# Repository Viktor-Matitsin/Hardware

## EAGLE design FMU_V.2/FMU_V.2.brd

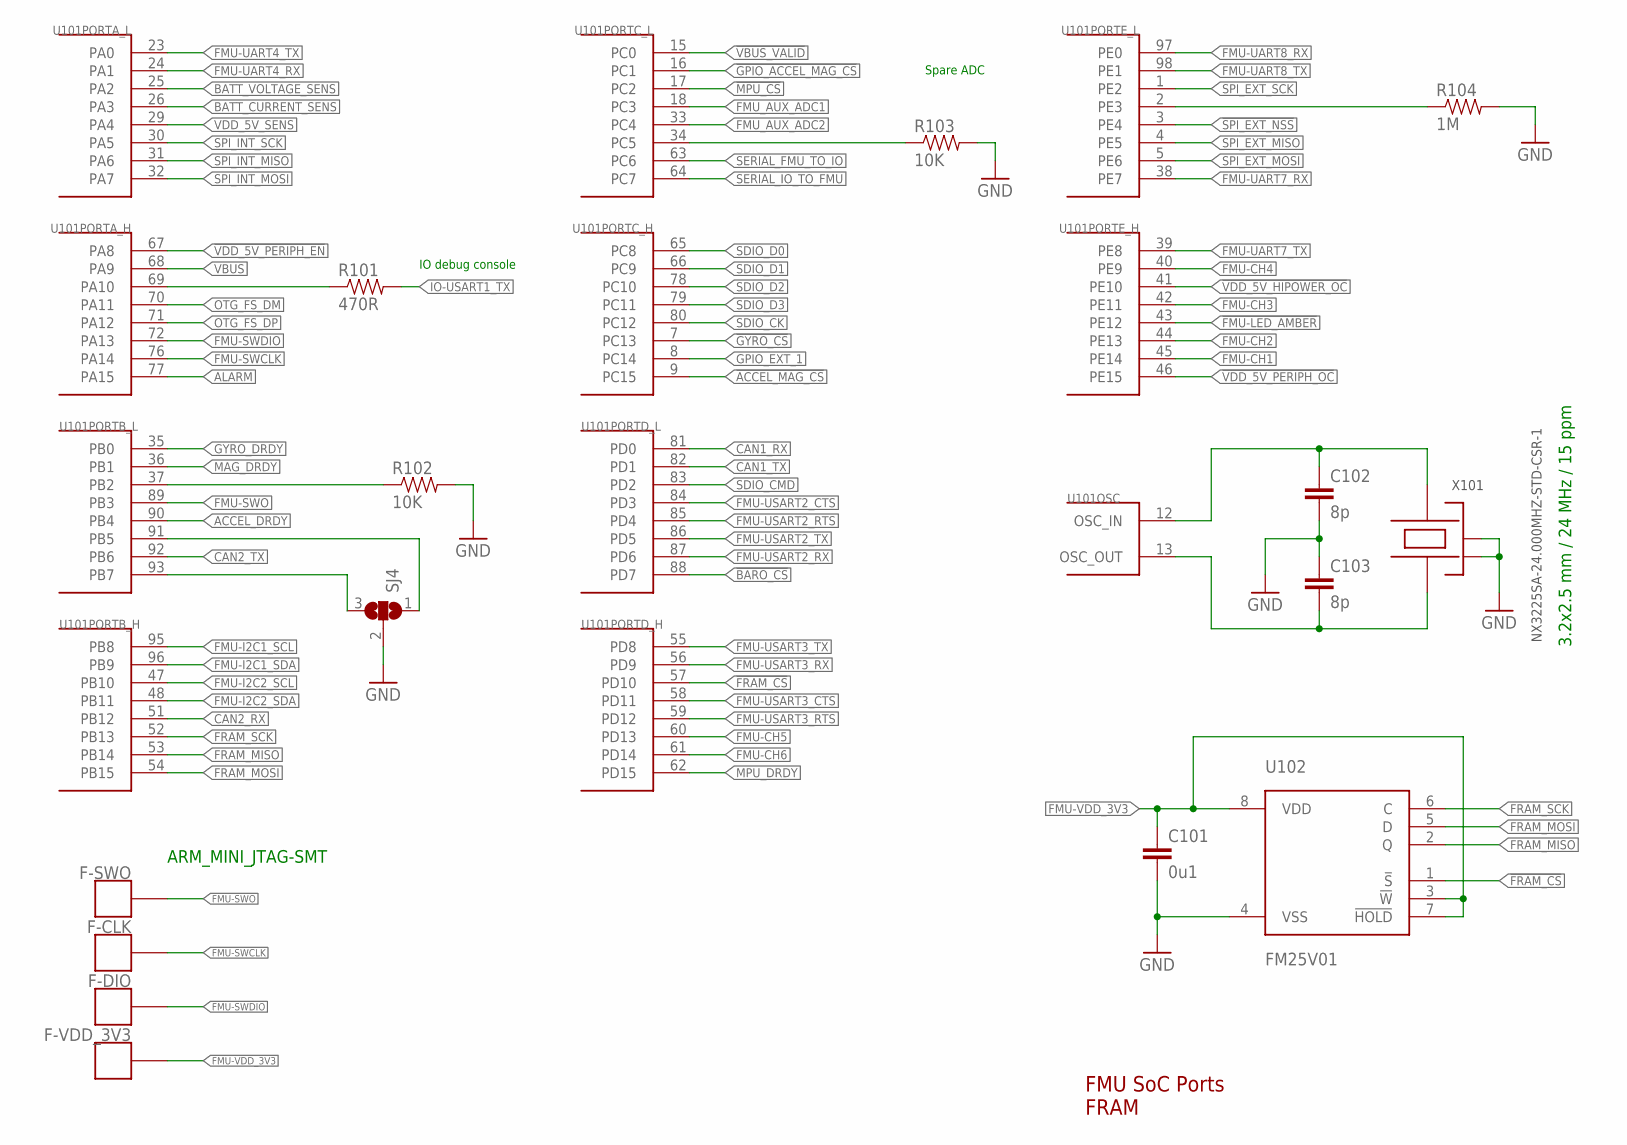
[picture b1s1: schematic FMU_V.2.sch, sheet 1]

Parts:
C101: 0u1; 0603-CAP
C102, C103: 8p; 0603-CAP
F-CLK: PAD.04; PAD.04X.04
F-DIO: PAD.04; PAD.04X.04
F-SWO: PAD.04; PAD.04X.04
F-VDD_3V3: PAD.04; PAD.04X.04
R101: 470R; 0603-RES
R102, R103: 10K; 0603-RES
R104: 1M; 0603-RES
SJ4: SJ2W; SJ_2
U101: STM32F4X7VX; TQFP100; PARTNO STM32F427VI
U102: FM25V01; SO08; PARTNO FM25V01-G
X101: NX3225SA-24.000MHZ-STD-CSR-1; OSCILLATOR-3.2X2.5; PARTNO NX3225SA-24.000000MHZ

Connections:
!ACCEL_MAG_CS: U101.9 (PC15); also elsewhere on the board
!BARO_CS: U101.88 (PD7); also elsewhere on the board
!FMU-LED_AMBER: U101.43 (PE12); also elsewhere on the board
!FRAM_CS: U101.57 (PD10), U102.1 (!S)
!GPIO_ACCEL_MAG_CS: U101.16 (PC1); also elsewhere on the board
!GYRO_CS: U101.7 (PC13); also elsewhere on the board
!MPU_CS: U101.17 (PC2); also elsewhere on the board
!SPI_EXT_NSS: U101.3 (PE4); also elsewhere on the board
!VBUS_VALID: U101.15 (PC0)
!VDD_5V_HIPOWER_OC: U101.41 (PE10); also elsewhere on the board
!VDD_5V_PERIPH_EN: U101.67 (PA8); also elsewhere on the board
!VDD_5V_PERIPH_OC: U101.46 (PE15); also elsewhere on the board
!VDD_BRICK_VALID: SJ4.1, U101.91 (PB5)
!VDD_SERVO_VALID: SJ4.3, U101.93 (PB7)
ACCEL_DRDY: U101.90 (PB4); also elsewhere on the board
ALARM: U101.77 (PA15); also elsewhere on the board
BATT_CURRENT_SENS: U101.26 (PA3); also elsewhere on the board
BATT_VOLTAGE_SENS: U101.25 (PA2); also elsewhere on the board
CAN1_RX: U101.81 (PD0); also elsewhere on the board
CAN1_TX: U101.82 (PD1); also elsewhere on the board
CAN2_RX: U101.51 (PB12); also elsewhere on the board
CAN2_TX: U101.92 (PB6); also elsewhere on the board
FMU-CH1: U101.45 (PE14); also elsewhere on the board
FMU-CH2: U101.44 (PE13); also elsewhere on the board
FMU-CH3: U101.42 (PE11); also elsewhere on the board
FMU-CH4: U101.40 (PE9); also elsewhere on the board
FMU-CH5: U101.60 (PD13); also elsewhere on the board
FMU-CH6: U101.61 (PD14); also elsewhere on the board
FMU-I2C1_SCL: U101.95 (PB8); also elsewhere on the board
FMU-I2C1_SDA: U101.96 (PB9); also elsewhere on the board
FMU-I2C2_SCL: U101.47 (PB10); also elsewhere on the board
FMU-I2C2_SDA: U101.48 (PB11); also elsewhere on the board
FMU-SWCLK: F-CLK.P$1, U101.76 (PA14)
FMU-SWDIO: F-DIO.P$1, U101.72 (PA13)
FMU-SWO: F-SWO.P$1, U101.89 (PB3)
FMU-UART4_RX: U101.24 (PA1); also elsewhere on the board
FMU-UART4_TX: U101.23 (PA0); also elsewhere on the board
FMU-UART7_RX: U101.38 (PE7); also elsewhere on the board
FMU-UART7_TX: U101.39 (PE8); also elsewhere on the board
FMU-UART8_RX: U101.97 (PE0); also elsewhere on the board
FMU-UART8_TX: U101.98 (PE1); also elsewhere on the board
FMU-USART2_CTS: U101.84 (PD3); also elsewhere on the board
FMU-USART2_RTS: U101.85 (PD4); also elsewhere on the board
FMU-USART2_RX: U101.87 (PD6); also elsewhere on the board
FMU-USART2_TX: U101.86 (PD5); also elsewhere on the board
FMU-USART3_CTS: U101.58 (PD11)
FMU-USART3_RTS: U101.59 (PD12)
FMU-USART3_RX: U101.56 (PD9); also elsewhere on the board
FMU-USART3_TX: U101.55 (PD8); also elsewhere on the board
FMU-VDD_3V3: C101.P$1 (1), F-VDD_3V3.P$1, U102.3 (!W), U102.7 (!HOLD), U102.8 (VDD); also elsewhere on the board
FMU_AUX_ADC1: U101.18 (PC3); also elsewhere on the board
FMU_AUX_ADC2: U101.33 (PC4); also elsewhere on the board
FRAM_MISO: U101.53 (PB14), U102.2 (Q)
FRAM_MOSI: U101.54 (PB15), U102.5 (D)
FRAM_SCK: U101.52 (PB13), U102.6 (C)
GND: C101.P$2 (2), C102.P$2 (2), C103.P$1 (1), R102.2, R103.2, R104.2, SJ4.2, U102.4 (VSS), X101.2 (NC_2), X101.4 (NC_4); also elsewhere on the board
GPIO_EXT_1: U101.8 (PC14); also elsewhere on the board
GYRO_DRDY: U101.35 (PB0); also elsewhere on the board
IO-USART1_TX: R101.2; also elsewhere on the board
MAG_DRDY: U101.36 (PB1); also elsewhere on the board
MPU_DRDY: U101.62 (PD15); also elsewhere on the board
unnamed: C103.P$2 (2), U101.13 (OSC_OUT), X101.1
unnamed: C102.P$1 (1), U101.12 (OSC_IN), X101.3
unnamed: R104.1, U101.2 (PE3)
unnamed: R103.1, U101.34 (PC5)
unnamed: R101.1, U101.69 (PA10)
OTG_FS_DM: U101.70 (PA11); also elsewhere on the board
OTG_FS_DP: U101.71 (PA12); also elsewhere on the board
PC5: R102.1, U101.37 (PB2)
SDIO_CK: U101.80 (PC12); also elsewhere on the board
SDIO_CMD: U101.83 (PD2); also elsewhere on the board
SDIO_D0: U101.65 (PC8); also elsewhere on the board
SDIO_D1: U101.66 (PC9); also elsewhere on the board
SDIO_D2: U101.78 (PC10); also elsewhere on the board
SDIO_D3: U101.79 (PC11); also elsewhere on the board
SERIAL_FMU_TO_IO: U101.63 (PC6); also elsewhere on the board
SERIAL_IO_TO_FMU: U101.64 (PC7); also elsewhere on the board
SPI_EXT_MISO: U101.4 (PE5); also elsewhere on the board
SPI_EXT_MOSI: U101.5 (PE6); also elsewhere on the board
SPI_EXT_SCK: U101.1 (PE2); also elsewhere on the board
SPI_INT_MISO: U101.31 (PA6); also elsewhere on the board
SPI_INT_MOSI: U101.32 (PA7); also elsewhere on the board
SPI_INT_SCK: U101.30 (PA5); also elsewhere on the board
VBUS: U101.68 (PA9); also elsewhere on the board
VDD_5V_SENS: U101.29 (PA4); also elsewhere on the board

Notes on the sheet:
FMU SoC Ports FRAM
IO debug console
Spare ADC
3.2x2.5 mm / 24 MHz / 15 ppm
ARM_MINI_JTAG-SMT

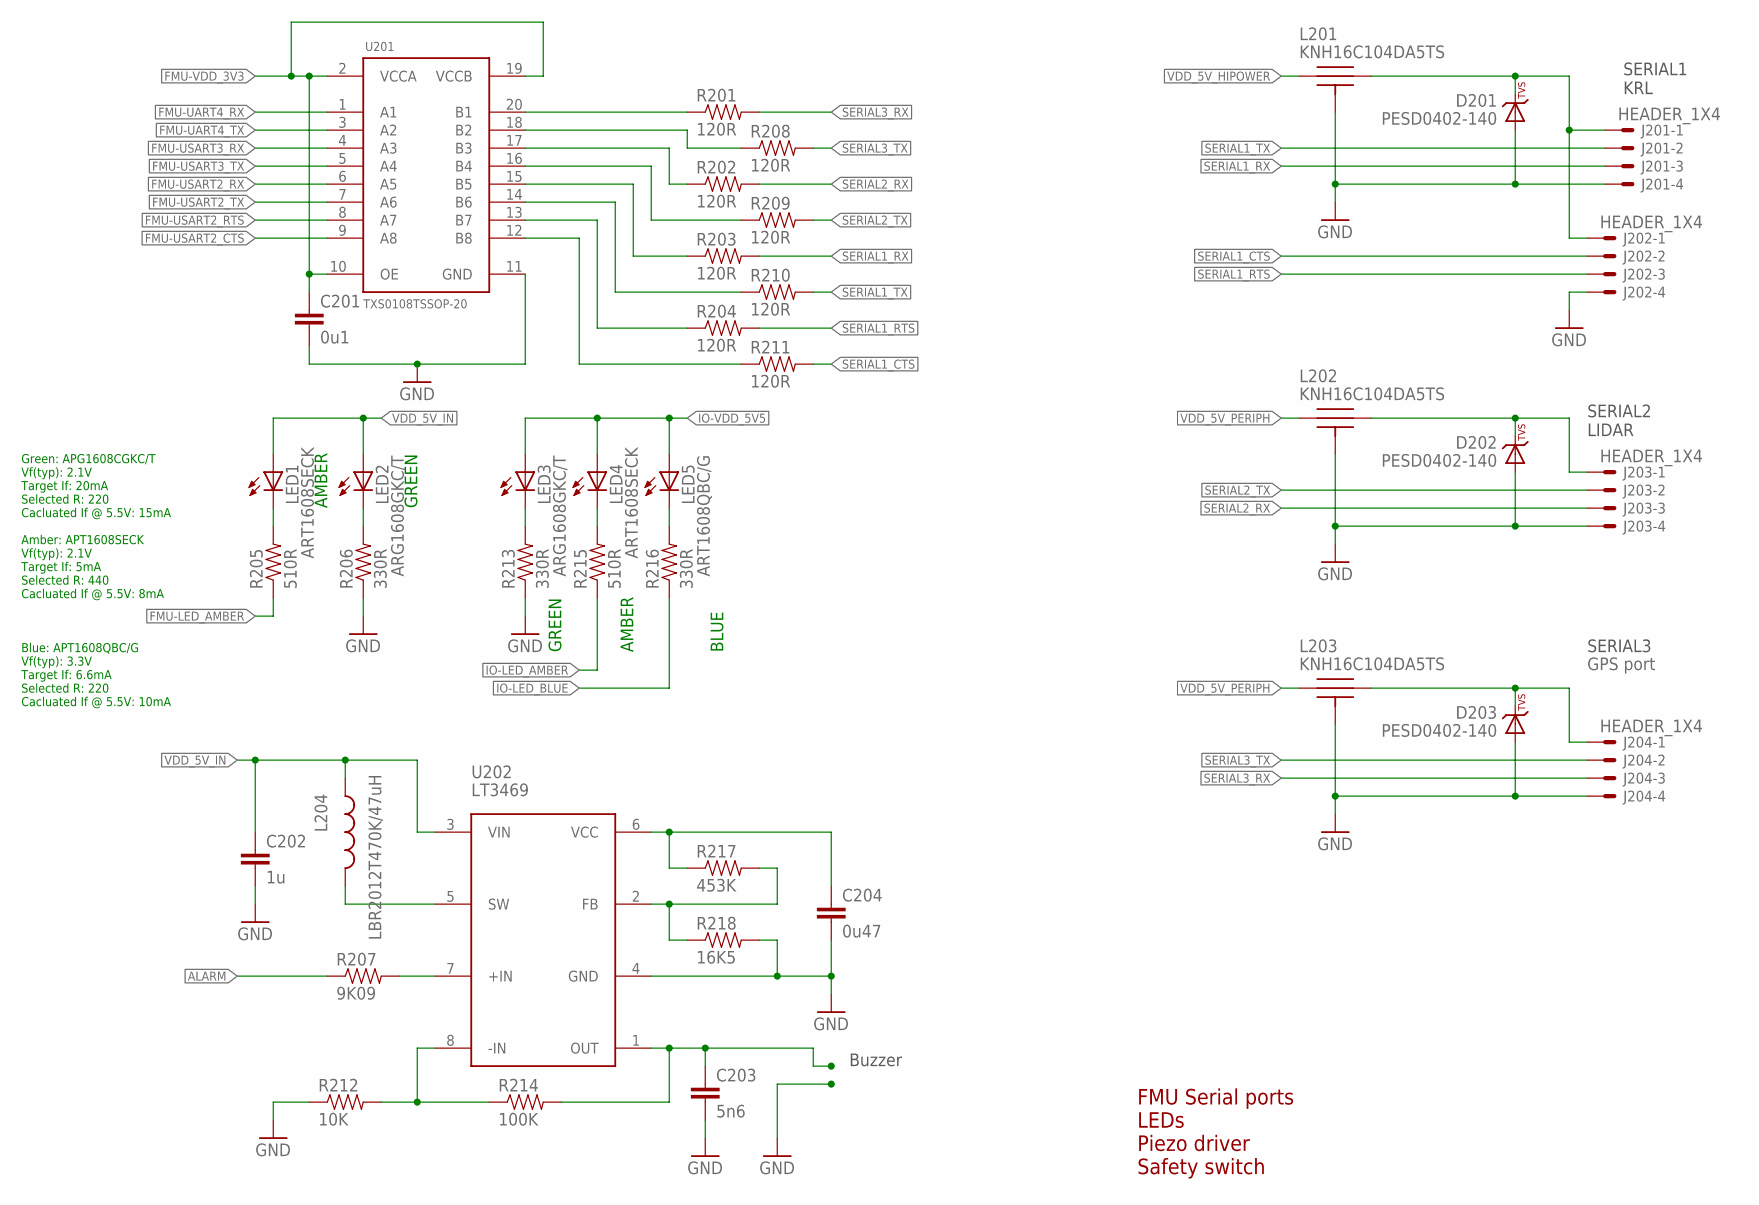
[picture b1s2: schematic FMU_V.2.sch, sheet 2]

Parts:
C201: 0u1; 0603-CAP
C202: 1u; 0603-CAP
C203: 5n6; 0603-CAP
C204: 0u47; 0603-CAP
D201, D202, D203: PESD0402-140; 0402-TVS; PARTNO PESD0402-140
J201, J202, J203, J204: HEADER_1X4; HEADER_2.54MM-1X04
L201, L202, L203: KNH16C104DA5TS; KYOCERA-KNH16-DA; PARTNO KNH16C104DA5TS
L204: LBR2012T470K/47uH; 0805-IND
LED1, LED4: ART1608SECK; 0603-LED
LED2, LED3: ARG1608GKC/T; 0603-LED
LED5: ART1608QBC/G; 0603-LED
R201, R202, R203, R204, R208, R209, R210, R211: 120R; 0603-RES
R205, R215: 510R; 0603-RES
R206, R213, R216: 330R; 0603-RES
R207: 9K09; 0603-RES
R212: 10K; 0603-RES
R214: 100K; 0603-RES
R217: 453K; 0603-RES
R218: 16K5; 0603-RES
U201: TXS0108TSSOP-20; R-PDSO-G20
U202: LT3469; SOT23-8

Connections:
!FMU-LED_AMBER: R205.1; also elsewhere on the board
!IO-LED_AMBER: R215.1; also elsewhere on the board
!IO-LED_BLUE: R216.1; also elsewhere on the board
ALARM: R207.1; also elsewhere on the board
FMU-UART4_RX: U201.1 (A1); also elsewhere on the board
FMU-UART4_TX: U201.3 (A2); also elsewhere on the board
FMU-USART2_CTS: U201.9 (A8); also elsewhere on the board
FMU-USART2_RTS: U201.8 (A7); also elsewhere on the board
FMU-USART2_RX: U201.6 (A5); also elsewhere on the board
FMU-USART2_TX: U201.7 (A6); also elsewhere on the board
FMU-USART3_RX: U201.4 (A3); also elsewhere on the board
FMU-USART3_TX: U201.5 (A4); also elsewhere on the board
FMU-VDD_3V3: C201.P$1 (1), U201.2 (VCCA), U201.10 (OE), U201.19 (VCCB); also elsewhere on the board
GND: C201.P$2 (2), C202.P$2 (2), C203.P$2 (2), C204.P$2 (2), D201.A, D202.A, D203.A, J201.4, J202.4, J203.4, J204.4, L201.P$3, L201.P$4, L201.P$5, L202.P$3, L202.P$4, L202.P$5, L203.P$3, L203.P$4, L203.P$5, R206.1, R212.1, R213.1, R218.2, U201.11 (GND), U202.4 (GND); also elsewhere on the board
IO-VDD_5V5: LED3.A, LED4.A, LED5.A; also elsewhere on the board
unnamed: D201.C, J201.1, J202.1, L201.P$2
unnamed: R201.1, U201.20 (B1)
unnamed: R208.1, U201.18 (B2)
unnamed: R202.1, U201.17 (B3)
unnamed: R209.1, U201.16 (B4)
unnamed: R203.1, U201.15 (B5)
unnamed: R210.1, U201.14 (B6)
unnamed: R204.1, U201.13 (B7)
unnamed: R211.1, U201.12 (B8)
unnamed: LED1.C, R205.2
unnamed: LED2.C, R206.2
unnamed: L204.P$2 (2), U202.5 (SW)
unnamed: LED3.C, R213.2
unnamed: LED4.C, R215.2
unnamed: LED5.C, R216.2
unnamed: D203.C, J204.1, L203.P$2
unnamed: D202.C, J203.1, L202.P$2
unnamed: C203.P$1 (1), R214.2, U202.1 (OUT)
unnamed: R207.2, U202.7 (+IN)
unnamed: R212.2, R214.1, U202.8 (-IN)
unnamed: C204.P$1 (1), R217.1, U202.6 (VCC)
unnamed: R217.2, R218.1, U202.2 (FB)
SERIAL1_CTS: J202.2, R211.2
SERIAL1_RTS: J202.3, R204.2
SERIAL1_RX: J201.3, R203.2
SERIAL1_TX: J201.2, R210.2
SERIAL2_RX: J203.3, R202.2
SERIAL2_TX: J203.2, R209.2
SERIAL3_RX: J204.3, R201.2
SERIAL3_TX: J204.2, R208.2
VDD_5V_HIPOWER: L201.P$1; also elsewhere on the board
VDD_5V_IN: C202.P$1 (1), L204.P$1 (1), LED1.A, LED2.A, U202.3 (VIN); also elsewhere on the board
VDD_5V_PERIPH: L202.P$1, L203.P$1; also elsewhere on the board

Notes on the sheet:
FMU Serial ports LEDs Piezo driver Safety switch
SERIAL2 LIDAR
SERIAL1 KRL
SERIAL3
GPS port
Green: APG1608CGKC/T Vf(typ): 2.1V Target If: 20mA Selected R: 220 Cacluated If @ 5.5V: 15mA Amber: APT1608SECK Vf(typ): 2.1V Target If: 5mA Selected R: 440 Cacluated If @ 5.5V: 8mA Blue: APT1608QBC/G Vf(typ): 3.3V Target If: 6.6mA Selected R: 220 Cacluated If @ 5.5V: 10mA
Buzzer
AMBER
GREEN
BLUE

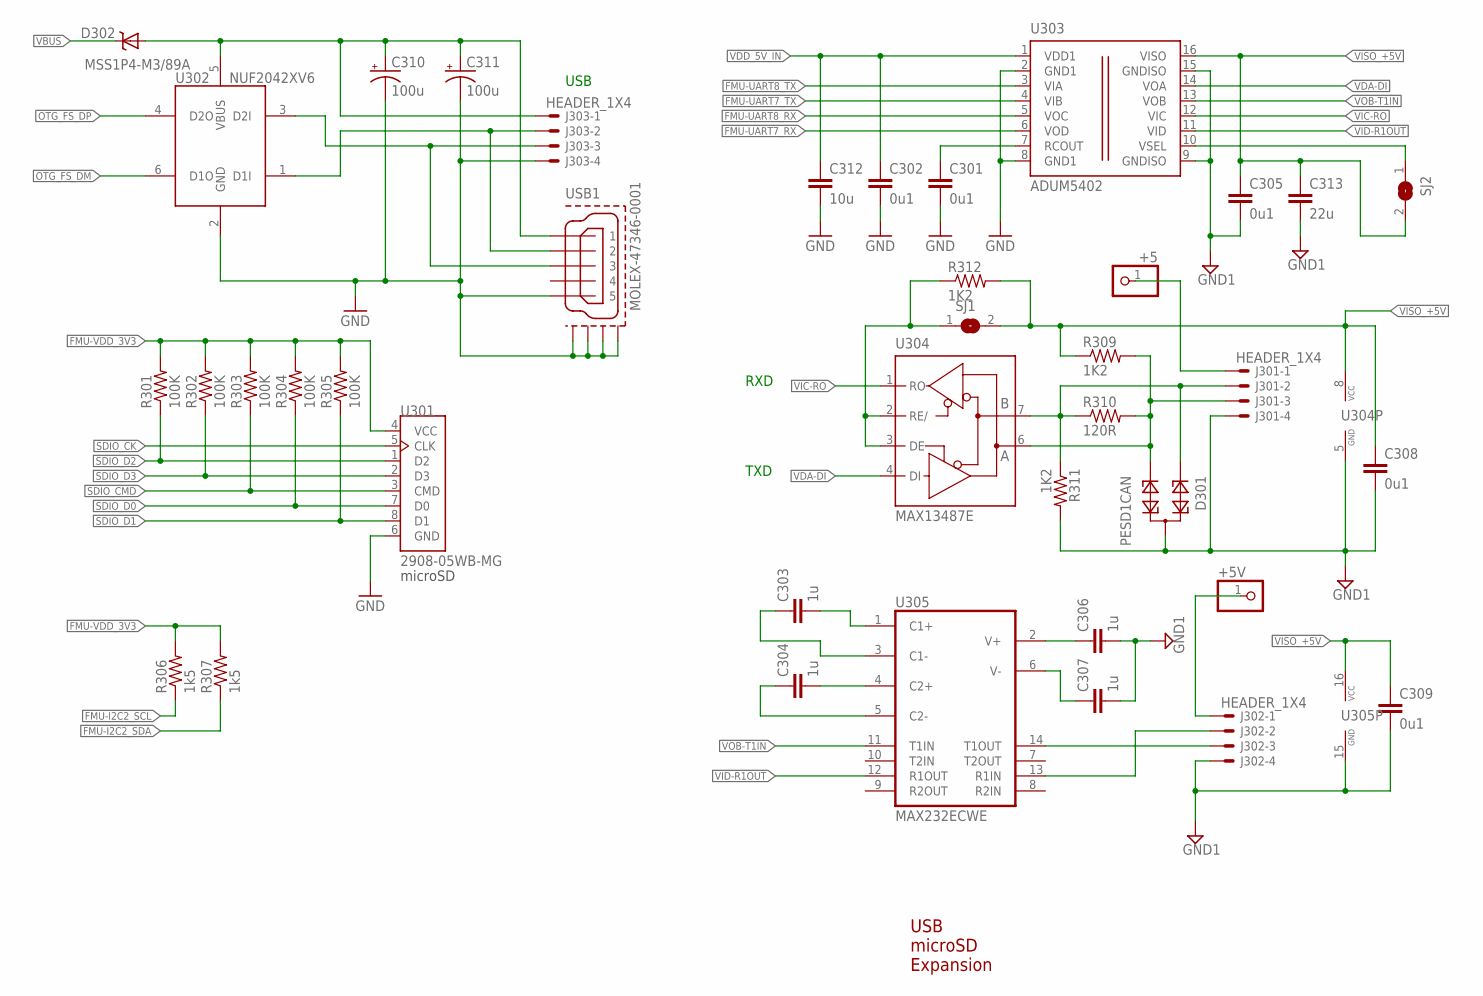
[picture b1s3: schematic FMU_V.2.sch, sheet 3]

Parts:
+5, +5V: PINHD-1X1; 1X01
C301, C302, C305, C308, C309: 0u1; 0603-CAP
C303, C304, C306, C307: 1u; 0805-CAP
C310, C311: 100u; EIA3216
C312: 10u; 0805-CAP
C313: 22u; 0805-CAP
D301: PESD1CAN; SOT23
D302: MSS1P4-M3/89A; MICROSMP
J301, J302, J303: HEADER_1X4; HEADER_2.54MM-1X04
R301, R302, R303, R304, R305: 100K; 0603-RES
R306, R307: 1k5; 0603-RES
R309, R311, R312: 1K2; 0603-RES
R310: 120R; 0805
SJ1, SJ2: SJ
U301: 2908-05WB-MG; MICROSD; PARTNO 2908-05WB-MG
U302: NUF2042XV6; SOT563-6; PARTNO NUF2042XV6T1G
U303: ADUM5402; SO-16W
U304: MAX13487E; SO08
U305: MAX232ECWE; SO16L
USB1: MOLEX-47346-0001

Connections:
1: C310.A (+), C311.A (+), D302.ANODE (A), J303.1, U302.5 (VBUS), USB1.VBUS (1)
FMU-I2C2_SCL: R306.1; also elsewhere on the board
FMU-I2C2_SDA: R307.1; also elsewhere on the board
FMU-UART7_RX: U303.6 (VOD); also elsewhere on the board
FMU-UART7_TX: U303.4 (VIB); also elsewhere on the board
FMU-UART8_RX: U303.5 (VOC); also elsewhere on the board
FMU-UART8_TX: U303.3 (VIA); also elsewhere on the board
FMU-VDD_3V3: R301.2, R302.2, R303.2, R304.2, R305.2, R306.2, R307.2, U301.4 (VCC); also elsewhere on the board
GND: C301.P$2 (2), C302.P$2 (2), C310.C (-), C311.C (-), C312.P$2 (2), J303.4, U301.6 (GND), U302.2 (GND), U303.2 (GND1), U303.8 (GND1), USB1.GND (5), USB1.GND1, USB1.GND2, USB1.GND3, USB1.GND4; also elsewhere on the board
GND1: C305.P$2 (2), C306.P$2 (2), C307.P$2 (2), C308.P$2 (2), C309.P$2 (2), C313.P$2 (2), D301.3, J301.4, J302.4, R311.2, U303.9 (GNDISO), U303.15 (GNDISO), U304.5 (GND), U305.15 (GND); also elsewhere on the board
unnamed: SJ2.1, U303.10 (VSEL)
unnamed: C304.P$2 (2), U305.4 (C2+)
unnamed: C304.P$1 (1), U305.5 (C2-)
unnamed: C303.P$1 (1), U305.3 (C1-)
unnamed: R312.1, SJ1.1, U304.2 (RE/), U304.3 (DE)
unnamed: C301.P$1 (1), U303.7 (RCOUT)
unnamed: C303.P$2 (2), U305.1 (C1+)
unnamed: C306.P$1 (1), U305.2 (V+)
unnamed: D301.1, J301.2, R310.1, R311.1, U304.7 (B)
unnamed: D301.2, J301.3, R309.2, R310.2, U304.6 (A)
unnamed: C307.P$1 (1), U305.6 (V-)
unnamed: J302.3, U305.14 (T1OUT)
unnamed: J302.2, U305.13 (R1IN)
unnamed: +5.1, J301.1
unnamed: +5V.1, J302.1
OTG_DM1: J303.2, U302.1 (D1I), USB1.D- (2)
OTG_DP1: J303.3, U302.3 (D2I), USB1.D+ (3)
OTG_FS_DM: U302.6 (D1O); also elsewhere on the board
OTG_FS_DP: U302.4 (D2O); also elsewhere on the board
SDIO_CK: U301.5 (CLK); also elsewhere on the board
SDIO_CMD: R303.1, U301.3 (CMD); also elsewhere on the board
SDIO_D0: R304.1, U301.7 (D0); also elsewhere on the board
SDIO_D1: R305.1, U301.8 (D1); also elsewhere on the board
SDIO_D2: R301.1, U301.1 (D2); also elsewhere on the board
SDIO_D3: R302.1, U301.2 (D3); also elsewhere on the board
VBUS: D302.CATHODE (C); also elsewhere on the board
VDA-DI: U303.14 (VOA), U304.4 (DI)
VDD_5V_IN: C302.P$1 (1), C312.P$1 (1), U303.1 (VDD1); also elsewhere on the board
VIC-RO: U303.12 (VIC), U304.1 (RO)
VID-R1OUT: U303.11 (VID), U305.12 (R1OUT)
VISO_+5V: C305.P$1 (1), C308.P$1 (1), C309.P$1 (1), C313.P$1 (1), R309.1, R312.2, SJ1.2, SJ2.2, U303.16 (VISO), U304.8 (VCC), U305.16 (VCC)
VOB-T1IN: U303.13 (VOB), U305.11 (T1IN)

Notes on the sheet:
USB microSD Expansion
microSD
USB
RXD
TXD

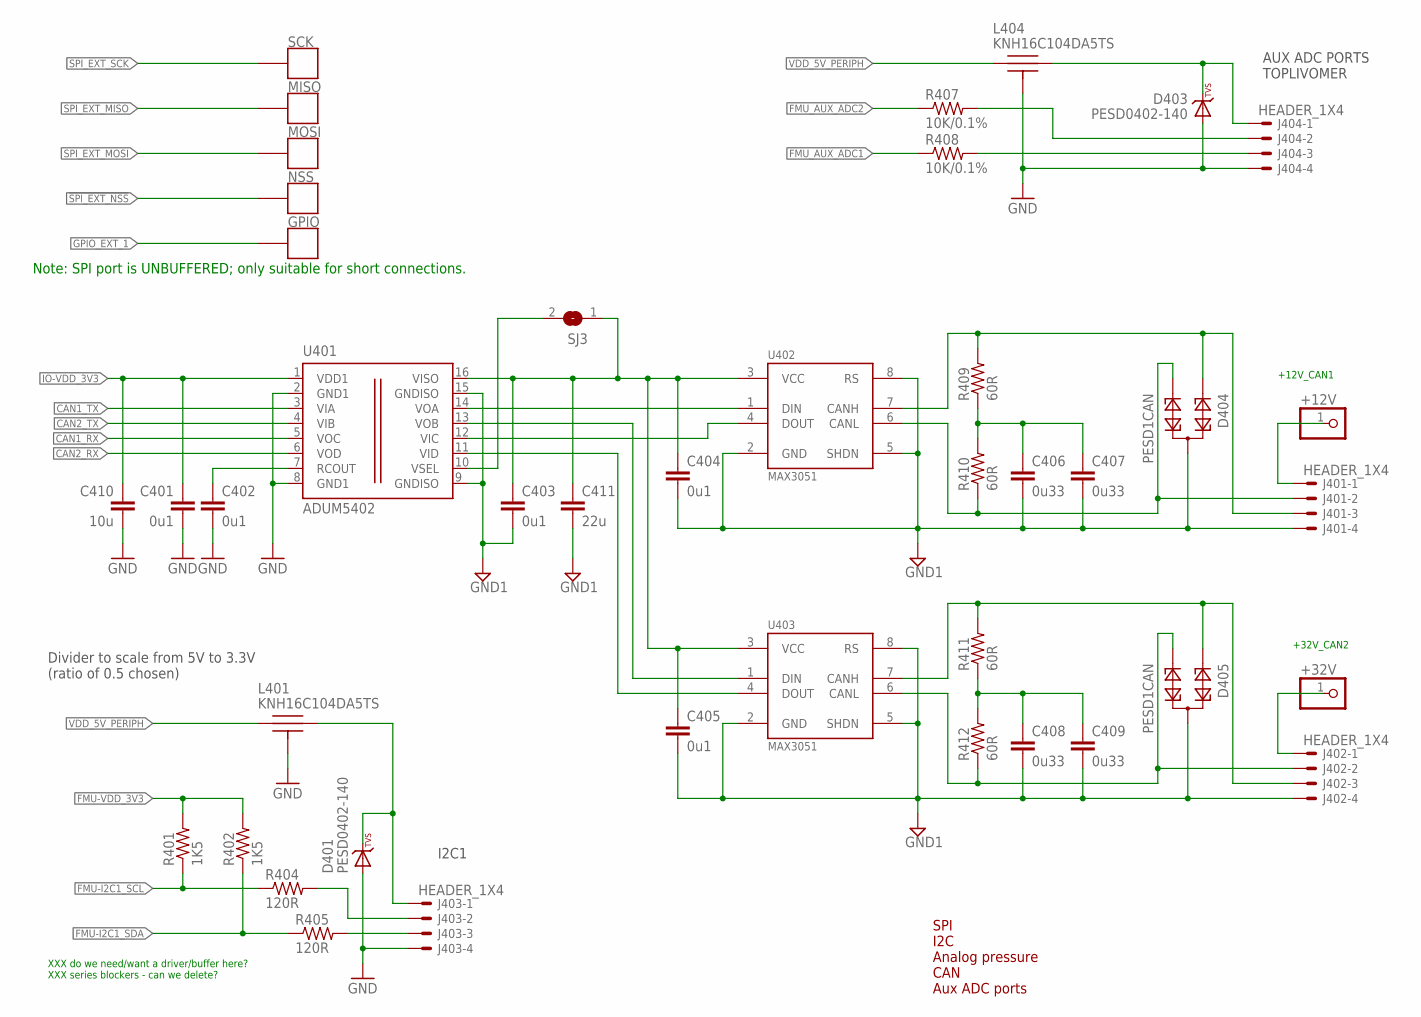
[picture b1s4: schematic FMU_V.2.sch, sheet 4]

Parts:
+12V, +32V: PINHD-1X1; 1X01
C401, C402, C403, C404, C405: 0u1; 0603-CAP
C406, C407, C408, C409: 0u33; 1210
C410: 10u; 0805-CAP
C411: 22u; 0805-CAP
D401, D403: PESD0402-140; 0402-TVS; PARTNO PESD0402-140
D404, D405: PESD1CAN; SOT23
GPIO: PAD.04; PAD.04X.04
J401, J402, J403, J404: HEADER_1X4; HEADER_2.54MM-1X04
L401, L404: KNH16C104DA5TS; KYOCERA-KNH16-DA; PARTNO KNH16C104DA5TS
MISO: PAD.04; PAD.04X.04
MOSI: PAD.04; PAD.04X.04
NSS: PAD.04; PAD.04X.04
R401, R402: 1K5; 0603-RES
R404, R405: 120R; 0603-RES
R407, R408: 10K/0.1%; 0603-RES
R409, R410, R411, R412: 60R; 0805
SCK: PAD.04; PAD.04X.04
SJ3: SJ
U401: ADUM5402; SO-16W
U402, U403: MAX3051; SOT23-8; PARTNO MAX3051EKA

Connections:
!SPI_EXT_NSS: NSS.P$1; also elsewhere on the board
CAN1_RX: U401.5 (VOC); also elsewhere on the board
CAN1_TX: U401.3 (VIA); also elsewhere on the board
CAN2_RX: U401.6 (VOD); also elsewhere on the board
CAN2_TX: U401.4 (VIB); also elsewhere on the board
FMU-I2C1_SCL: R401.1, R404.1; also elsewhere on the board
FMU-I2C1_SDA: R402.1, R405.1; also elsewhere on the board
FMU-VDD_3V3: R401.2, R402.2; also elsewhere on the board
FMU_AUX_ADC1: R408.1; also elsewhere on the board
FMU_AUX_ADC2: R407.1; also elsewhere on the board
FMU_AUX_ADC2_PROT: J404.2, R407.2
GND: C401.P$2 (2), C402.P$2 (2), C410.P$2 (2), D401.A, D403.A, J403.4, J404.4, L401.P$3, L401.P$4, L401.P$5, L404.P$3, L404.P$4, L404.P$5, U401.2 (GND1), U401.8 (GND1); also elsewhere on the board
GND1: C403.P$2 (2), C404.P$2 (2), C405.P$2 (2), C406.2, C407.2, C408.2, C409.2, C411.P$2 (2), D404.3, D405.3, J401.4, J402.4, U401.9 (GNDISO), U401.15 (GNDISO), U402.2 (GND), U402.5 (SHDN), U402.8 (RS), U403.2 (GND), U403.5 (SHDN), U403.8 (RS); also elsewhere on the board
GPIO_EXT_1: GPIO.P$1; also elsewhere on the board
IO-VDD_3V3: C401.P$1 (1), C410.P$1 (1), U401.1 (VDD1); also elsewhere on the board
unnamed: J404.3, R408.2
unnamed: C406.1, C407.1, R409.1, R410.2
unnamed: D405.1, J402.3, R411.2, U403.7 (CANH)
unnamed: D404.1, J401.3, R409.2, U402.7 (CANH)
unnamed: SJ3.2, U401.10 (VSEL)
unnamed: U401.13 (VOB), U403.1 (DIN)
unnamed: D405.2, J402.2, R412.1, U403.6 (CANL)
unnamed: D404.2, J401.2, R410.1, U402.6 (CANL)
unnamed: U401.14 (VOA), U402.1 (DIN)
unnamed: U401.12 (VIC), U402.4 (DOUT)
unnamed: U401.11 (VID), U403.4 (DOUT)
unnamed: C402.P$1 (1), U401.7 (RCOUT)
unnamed: J403.2, R404.2
unnamed: C408.1, C409.1, R411.1, R412.2
unnamed: J403.3, R405.2
unnamed: C403.P$1 (1), C404.P$1 (1), C405.P$1 (1), C411.P$1 (1), SJ3.1, U401.16 (VISO), U402.3 (VCC), U403.3 (VCC)
unnamed: D401.C, J403.1, L401.P$2
unnamed: D403.C, J404.1, L404.P$2
P1: +12V.1, J401.1
P2: +32V.1, J402.1
SPI_EXT_MISO: MISO.P$1; also elsewhere on the board
SPI_EXT_MOSI: MOSI.P$1; also elsewhere on the board
SPI_EXT_SCK: SCK.P$1; also elsewhere on the board
VDD_5V_PERIPH: L401.P$1, L404.P$1; also elsewhere on the board

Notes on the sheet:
XXX do we need/want a driver/buffer here? XXX series blockers - can we delete?
I2C1
AUX ADC PORTS TOPLIVOMER
SPI I2C Analog pressure CAN Aux ADC ports
Note: SPI port is UNBUFFERED; only suitable for short connections.
Divider to scale from 5V to 3.3V (ratio of 0.5 chosen)
+12V_CAN1
+32V_CAN2

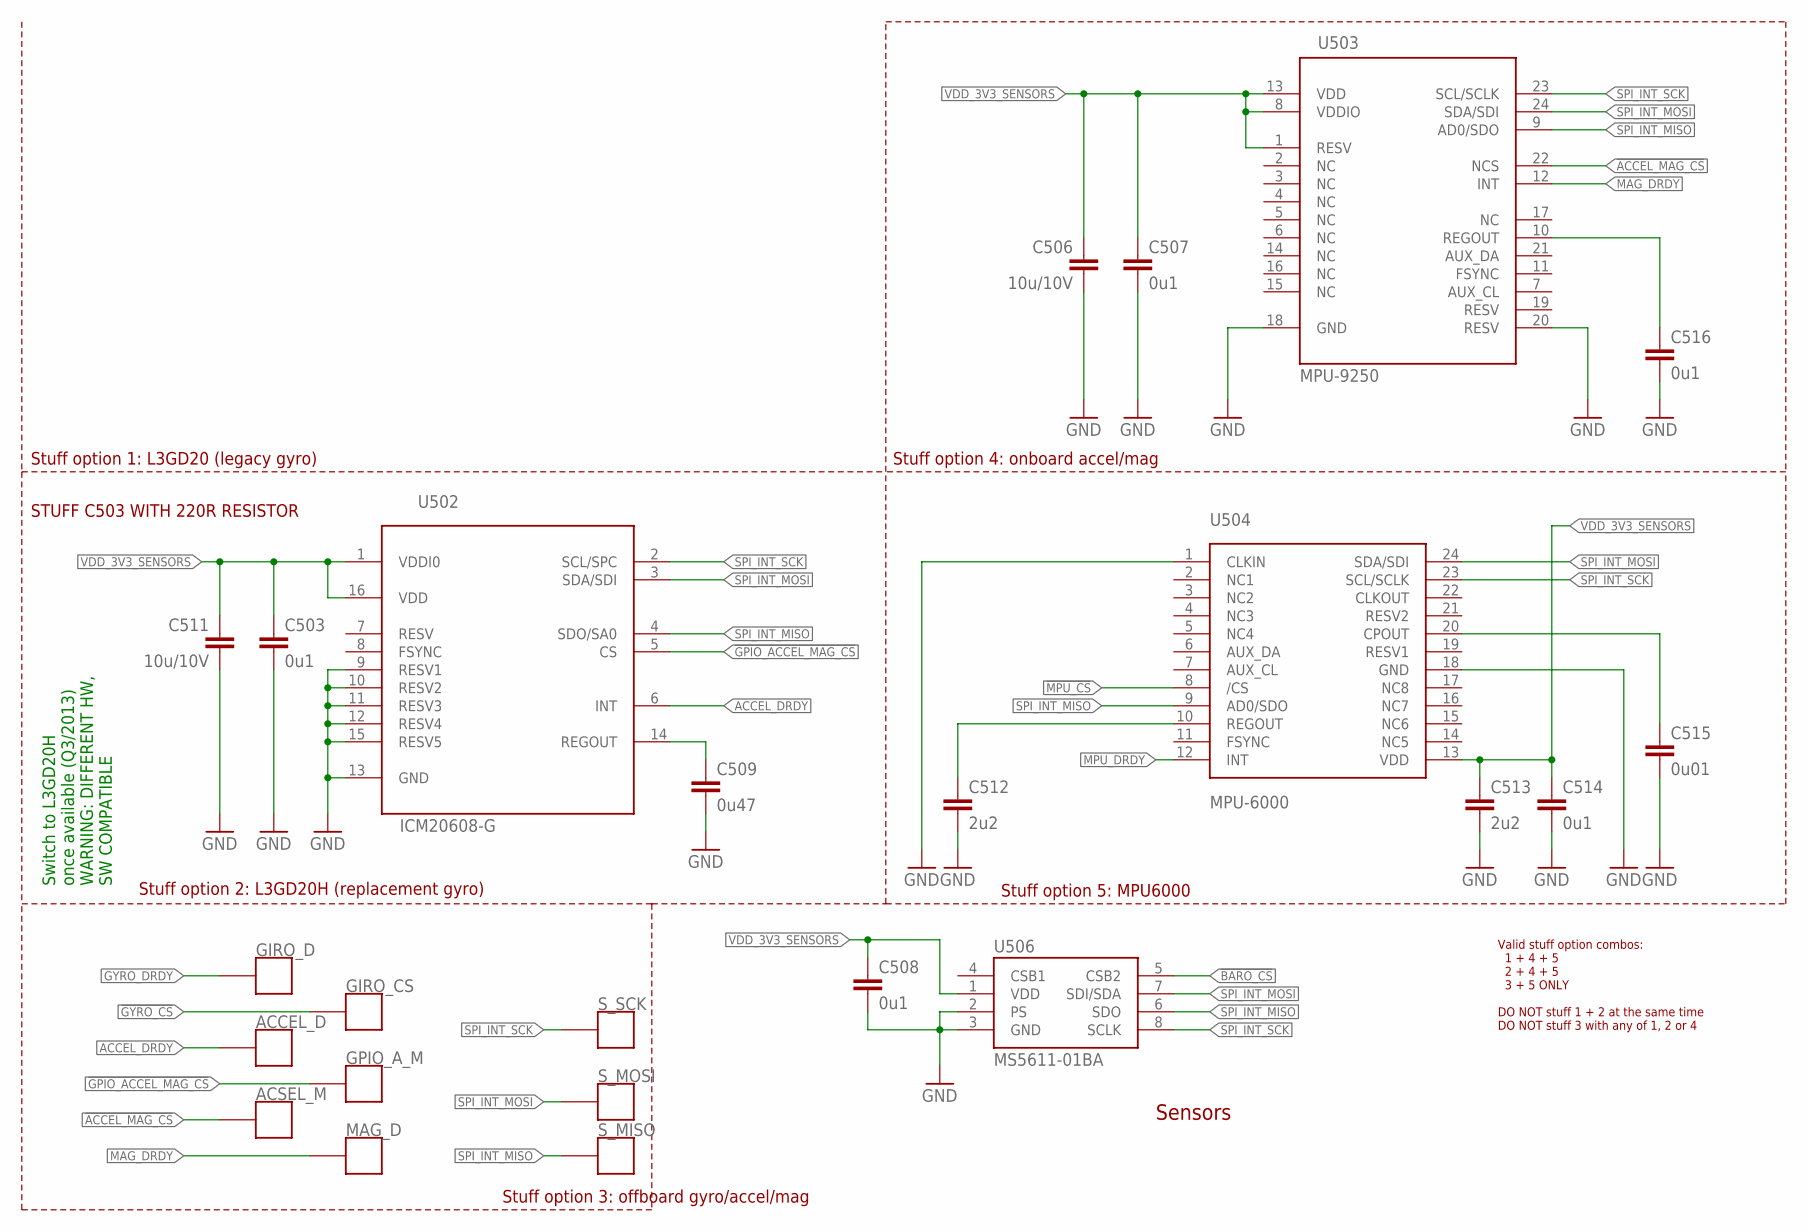
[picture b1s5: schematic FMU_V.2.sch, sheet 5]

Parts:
ACCEL_D: PAD.04; PAD.04X.04
ACSEL_M: PAD.04; PAD.04X.04
C503, C507, C508, C514, C516: 0u1; 0603-CAP
C506, C511: 10u/10V; 0805-CAP; PARTNO CC0805ZKY5V6BB106
C509: 0u47; 0603-CAP
C512, C513: 2u2; 0603-CAP; PARTNO C1608X6S1C225K080AC
C515: 0u01; 0603-CAP; PARTNO 06033C103JAT2A
GIRO_CS: PAD.04; PAD.04X.04
GIRO_D: PAD.04; PAD.04X.04
GPIO_A_M: PAD.04; PAD.04X.04
MAG_D: PAD.04; PAD.04X.04
S_MISO: PAD.04; PAD.04X.04
S_MOSI: PAD.04; PAD.04X.04
S_SCK: PAD.04; PAD.04X.04
U502: ICM20608-G; LGA-16-3PX5P
U503: MPU-9250; QFN
U504: MPU-6000; QFN-24; PARTNO MPU-6000
U506: MS5611-01BA; PARTNO MS5611-01BA

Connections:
!ACCEL_MAG_CS: ACSEL_M.P$1, U503.22 (NCS); also elsewhere on the board
!BARO_CS: U506.5 (CSB2); also elsewhere on the board
!GPIO_ACCEL_MAG_CS: GPIO_A_M.P$1, U502.5 (CS); also elsewhere on the board
!GYRO_CS: GIRO_CS.P$1; also elsewhere on the board
!MPU_CS: U504.8 (/CS); also elsewhere on the board
ACCEL_DRDY: ACCEL_D.P$1, U502.6 (INT); also elsewhere on the board
GND: C503.P$2 (2), C506.P$2 (2), C507.P$2 (2), C508.P$2 (2), C509.P$2 (2), C511.P$2 (2), C512.P$2 (2), C513.P$2 (2), C514.P$2 (2), C515.P$2 (2), C516.P$2 (2), U502.9 (RESV1), U502.10 (RESV2), U502.11 (RESV3), U502.12 (RESV4), U502.13 (GND), U502.15 (RESV5), U503.18 (GND), U503.20 (RESV), U504.1 (CLKIN), U504.18 (GND), U506.2 (PS), U506.3 (GND); also elsewhere on the board
GYRO_DRDY: GIRO_D.P$1; also elsewhere on the board
MAG_DRDY: MAG_D.P$1, U503.12 (INT); also elsewhere on the board
MPU_DRDY: U504.12 (INT); also elsewhere on the board
unnamed: C509.P$1 (1), U502.14 (REGOUT)
unnamed: C516.P$1 (1), U503.10 (REGOUT)
unnamed: C512.P$1 (1), U504.10 (REGOUT)
unnamed: C515.P$1 (1), U504.20 (CPOUT)
SPI_INT_MISO: S_MISO.P$1, U502.4 (SDO/SA0), U503.9 (AD0/SDO), U504.9 (AD0/SDO), U506.6 (SDO); also elsewhere on the board
SPI_INT_MOSI: S_MOSI.P$1, U502.3 (SDA/SDI), U503.24 (SDA/SDI), U504.24 (SDA/SDI), U506.7 (SDI/SDA); also elsewhere on the board
SPI_INT_SCK: S_SCK.P$1, U502.2 (SCL/SPC), U503.23 (SCL/SCLK), U504.23 (SCL/SCLK), U506.8 (SCLK); also elsewhere on the board
VDD_3V3_SENSORS: C503.P$1 (1), C506.P$1 (1), C507.P$1 (1), C508.P$1 (1), C511.P$1 (1), C513.P$1 (1), C514.P$1 (1), U502.1 (VDDI0), U502.16 (VDD), U503.1 (RESV), U503.8 (VDDIO), U503.13 (VDD), U504.13 (VDD), U506.1 (VDD); also elsewhere on the board

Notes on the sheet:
Sensors
Switch to L3GD20H once available (Q3/2013) WARNING: DIFFERENT HW, SW COMPATIBLE
Stuff option 1: L3GD20 (legacy gyro)
Stuff option 2: L3GD20H (replacement gyro)
Stuff option 4: onboard accel/mag
Valid stuff option combos: 1 + 4 + 5 2 + 4 + 5 3 + 5 ONLY DO NOT stuff 1 + 2 at the same time DO NOT stuff 3 with any of 1, 2 or 4
Stuff option 5: MPU6000
Stuff option 3: offboard gyro/accel/mag
STUFF C503 WITH 220R RESISTOR

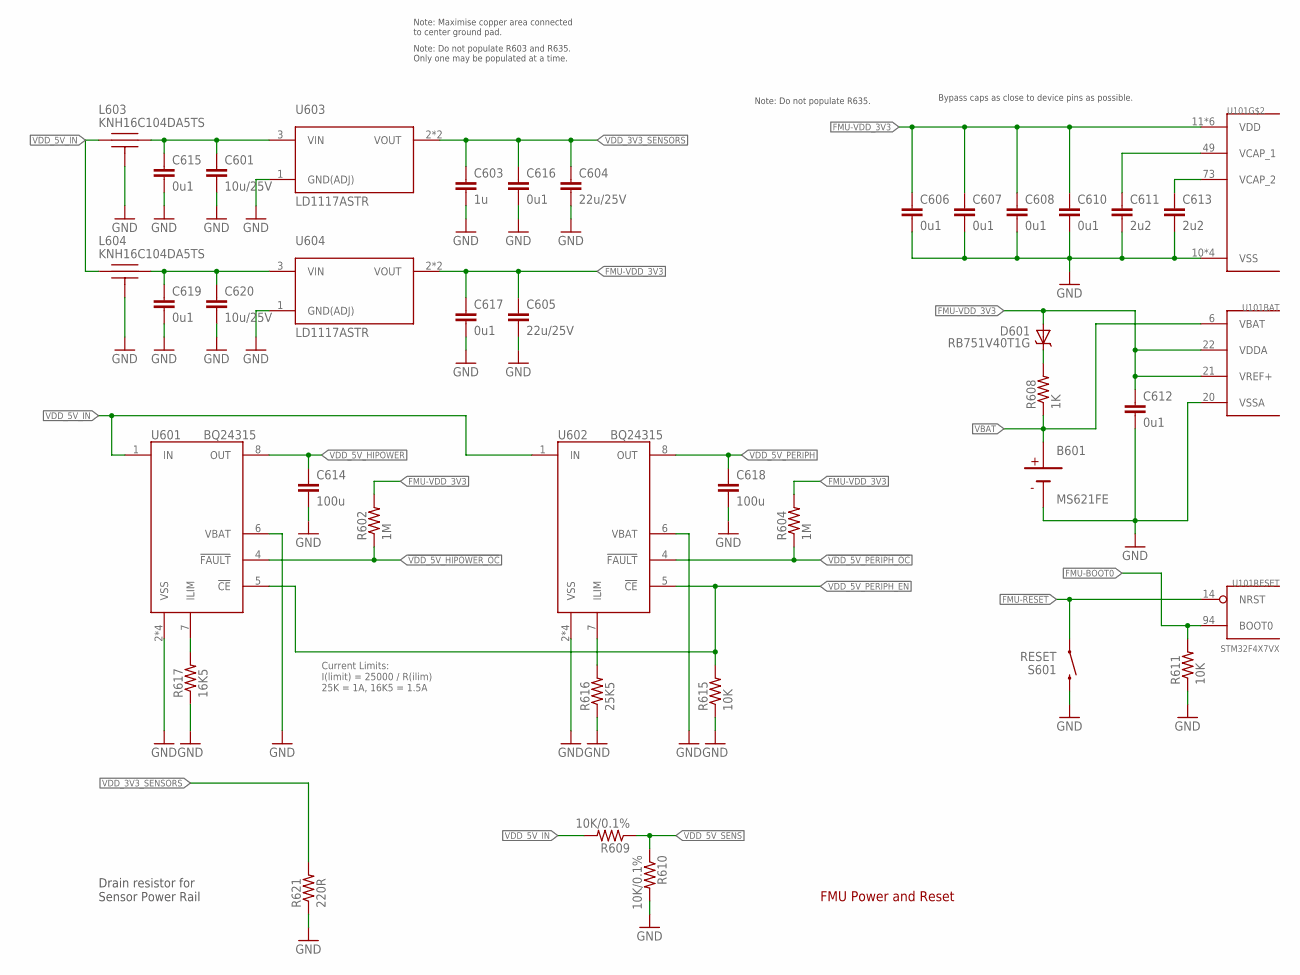
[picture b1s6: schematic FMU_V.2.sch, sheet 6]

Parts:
B601: MS621FE; PARTNO MS621FE-FL11E
C601, C620: 10u/25V; 0805-CAP; PARTNO CL21A106KAYNNNE
C603: 1u; 0603-CAP; PARTNO CC0603ZRY5V7BB105
C604, C605: 22u/25V; 0805-CAP; PARTNO CL21A226MAQNNNE
C606, C607, C608, C610, C612, C615, C616, C617, C619: 0u1; 0603-CAP
C611, C613: 2u2; 0603-CAP; PARTNO C1608X6S1C225K080AC
C614, C618: 100u; 1206-CAP; PARTNO C3216X5R1A107M160AC
D601: RB751V40T1G; SOD323
L603, L604: KNH16C104DA5TS; KYOCERA-KNH16-DA; PARTNO KNH16C104DA5TS
R602, R604: 1M; 0603-RES
R608: 1K; 0603-RES
R609, R610: 10K/0.1%; 0603-RES
R611, R615: 10K; 0603-RES
R616: 25K5; 0603-RES
R617: 16K5; 0603-RES
R621: 220R; 0603-RES
S601: RESET; EVQP7J01K; PARTNO EVQ-P7J01P
U101: STM32F4X7VX; TQFP100; PARTNO STM32F427VI
U601, U602: BQ24315; QFN8-DSG; PARTNO BQ24315DSGR
U603, U604: LD1117ASTR; SOT-223

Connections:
!VDD_5V_HIPOWER_OC: R602.1, U601.4 (!FAULT); also elsewhere on the board
!VDD_5V_PERIPH_EN: R615.2, U601.5 (!CE), U602.5 (!CE); also elsewhere on the board
!VDD_5V_PERIPH_OC: R604.1, U602.4 (!FAULT); also elsewhere on the board
FMU-!RESET: S601.A1 (1), U101.14 (NRST)
FMU-BOOT0: R611.2, U101.94 (BOOT0); also elsewhere on the board
FMU-VDD_3V3: C605.P$1 (1), C606.P$1 (1), C607.P$1 (1), C608.P$1 (1), C610.P$1 (1), C612.P$1 (1), C617.P$1 (1), D601.A, R602.2, R604.2, U101.11 (VDD), U101.19 (VDD), U101.21 (VREF+), U101.22 (VDDA), U101.28 (VDD), U101.50 (VDD), U101.75 (VDD), U101.100 (VDD), U604.2 (VOUT), U604.4 (VOUT); also elsewhere on the board
FMU-VDD_5V5: C601.P$1 (1), C615.P$1 (1), L603.P$2, U603.3 (VIN)
GND: B601.2 (NEG), C601.P$2 (2), C603.P$2 (2), C604.P$2 (2), C605.P$2 (2), C606.P$2 (2), C607.P$2 (2), C608.P$2 (2), C610.P$2 (2), C611.P$2 (2), C612.P$2 (2), C613.P$2 (2), C614.P$2 (2), C615.P$2 (2), C616.P$2 (2), C617.P$2 (2), C618.P$2 (2), C619.P$2 (2), C620.P$2 (2), L603.P$3, L603.P$4, L603.P$5, L604.P$3, L604.P$4, L604.P$5, R610.2, R611.1, R615.1, R616.1, R617.1, R621.1, S601.B3 (2), U101.10 (VSS), U101.20 (VSSA), U101.27 (VSS), U101.74 (VSS), U101.99 (VSS), U601.2 (VSS), U601.6 (VBAT), U601.GND (VSS), U601.P$2 (VSS), U601.P$3 (VSS), U602.2 (VSS), U602.6 (VBAT), U602.GND (VSS), U602.P$2 (VSS), U602.P$3 (VSS), U603.1 (GND(ADJ)), U604.1 (GND(ADJ)); also elsewhere on the board
unnamed: C613.P$1 (1), U101.73 (VCAP_2)
unnamed: C611.P$1 (1), U101.49 (VCAP_1)
unnamed: D601.C, R608.2
unnamed: C619.P$1 (1), C620.P$1 (1), L604.P$2, U604.3 (VIN)
unnamed: R616.2, U602.7 (ILIM)
unnamed: R617.2, U601.7 (ILIM)
VBAT: B601.1 (POS), R608.1, U101.6 (VBAT); also elsewhere on the board
VDD_3V3_SENSORS: C603.P$1 (1), C604.P$1 (1), C616.P$1 (1), R621.2, U603.2 (VOUT), U603.4 (VOUT); also elsewhere on the board
VDD_5V_HIPOWER: C614.P$1 (1), U601.8 (OUT); also elsewhere on the board
VDD_5V_IN: L603.P$1, L604.P$1, R609.2, U601.1 (IN), U602.1 (IN); also elsewhere on the board
VDD_5V_PERIPH: C618.P$1 (1), U602.8 (OUT); also elsewhere on the board
VDD_5V_SENS: R609.1, R610.1; also elsewhere on the board

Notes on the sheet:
FMU Power and Reset
Bypass caps as close to device pins as possible.
Note: Maximise copper area connected to center ground pad.
Current Limits: I(limit) = 25000 / R(ilim) 25K = 1A, 16K5 = 1.5A
Drain resistor for Sensor Power Rail
Note: Do not populate R603 and R635. Only one may be populated at a time.
Note: Do not populate R635.
